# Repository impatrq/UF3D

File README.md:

# Bienvenido a UpFeet

<div align="center">

🔗 Visitanos en  
👉 <a href="vzaccari33.wixsite.com/upfeet" target="_blank" rel="noopener noreferrer"><strong>nuestra pagina web</strong></a>

<br><br>

<a href="https://www.instagram.com/upfeet.3d/" target="_blank" rel="noopener noreferrer">
  
  @upfeet
</a>

</div>

---

## Nuestra Propuesta

**UpFeet3D** es un proyecto que desarrolla un escáner de pies basado en tecnología LiDAR y un sistema de ejes motorizados que permiten generar un modelo 3D preciso de la anatomía del pie. A partir de este escaneo, se diseña de manera automática una plantilla ortopédica personalizada que luego es fabricada mediante impresión 3D, ofreciendo una solución innovadora, accesible y adaptada a cada usuario.

---

## Cómo surgió el proyecto

El proyecto surgió a partir de la necesidad de brindar una solución a los pilotos y tripulaciones aéreas, quienes pasan largas horas sentados en condiciones que, sumadas a una mala pisada, pueden afectar la postura, generar dolores en la columna y aumentar la fatiga. Para atender esta problemática se diseñó un escáner portátil, que permite a una aerolínea contar con una sola máquina capaz de realizar plantillas personalizadas a todos sus empleados, reduciendo costos y facilitando la implementación. Con el tiempo, el desarrollo se proyectó también para otros usos, ofreciendo beneficios a cualquier persona que requiera una corrección postural o mayor confort en su andar.

---

## Características Principales

- Impresión 3D  
- Configuración por pantalla táctil  
- Escaneo 3D LiDAR  
- Sistema de ejes  
- Portátil  
- Económico  
- Rápido  

---

## Integrantes

- Melina Alfonso  
- Agustín Azorín  
- Eugenio Herrera  
- Tiago López  
- Victoria Viva  
- Valentín Zaccari  

---

## Información de Contacto

🌐 Sitio web oficial: [UpFeet Web](vzaccari33.wixsite.com/upfeet)  
📸 Instagram: [@UpFeet](https://www.instagram.com/upfeet.3d/) 📱🙌🎉  
📧 Correo: **upfeet3d@gmail.com**

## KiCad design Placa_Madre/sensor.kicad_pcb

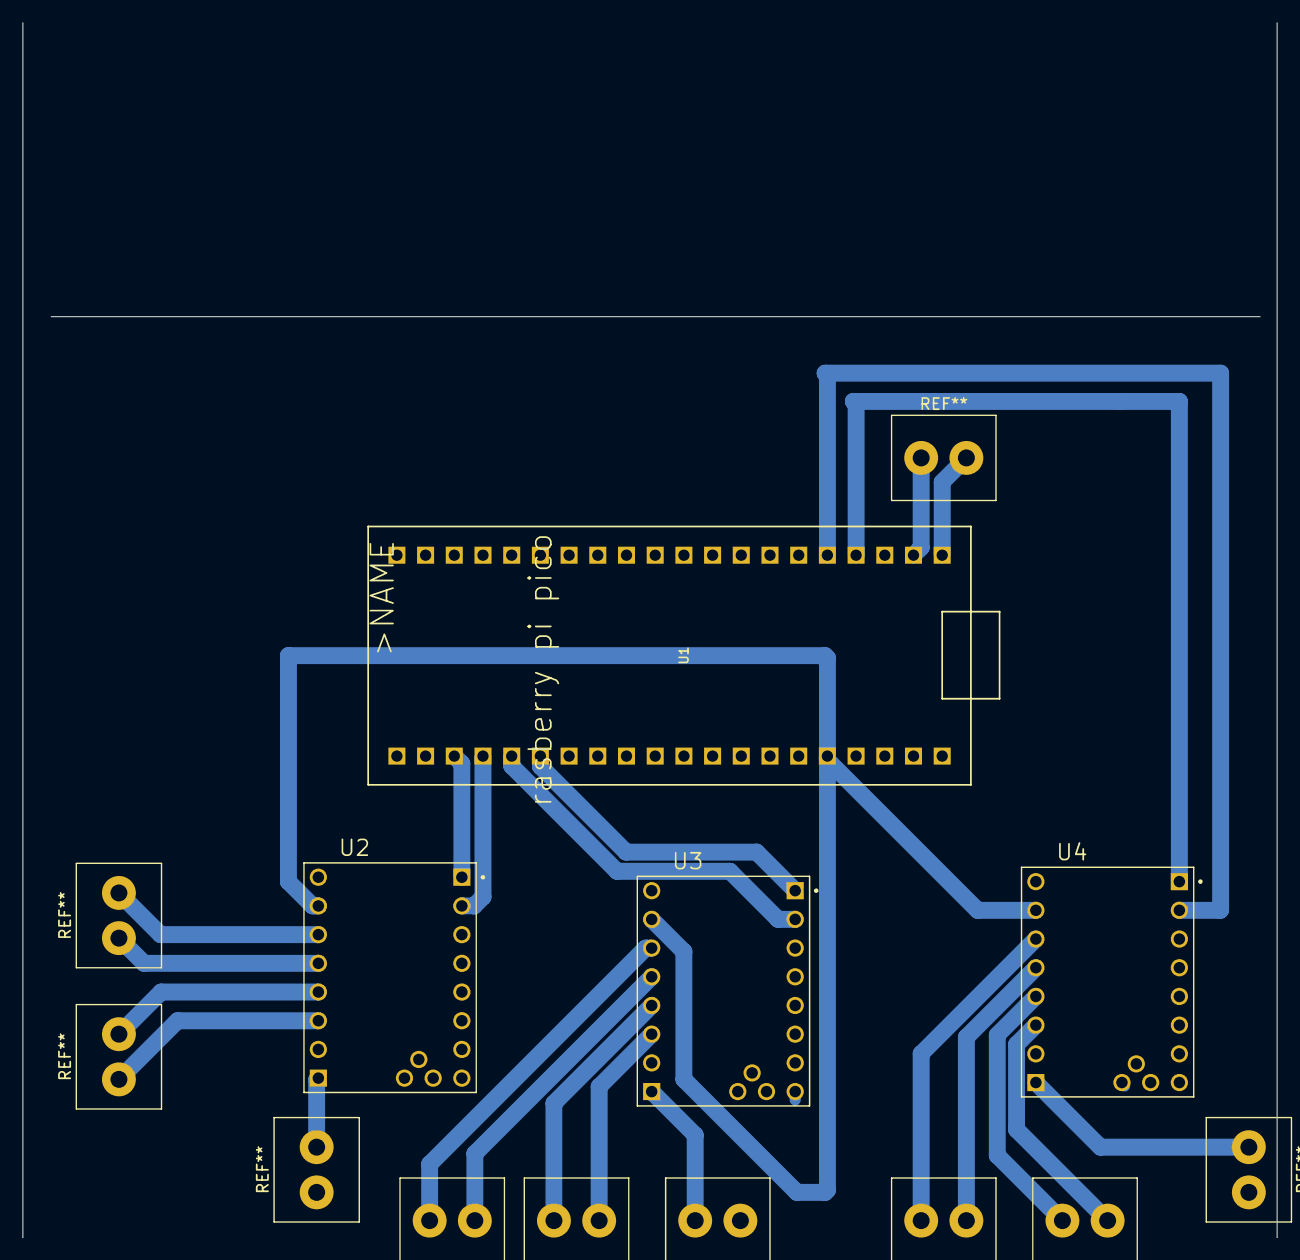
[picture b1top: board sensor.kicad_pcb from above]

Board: 2 copper layers, 111.0 x 107.5 mm, 4 parts (0 on the bottom side), 8 nets.

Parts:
U1: RASPBERRY_PI_PICO
U2, U3, U4: TMC2208_SILENTSTEPSTICK; MODULE_TMC2208_SILENTSTEPSTICK

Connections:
DIR: U1.GND3, U2.JP1_1 (DIR)
DIR2: U1.GP19, U3.JP1_2 (STEP)
DIR3: U1.GP2, U1.GP21, U4.JP1_1 (DIR)
GND: U1.GND, U2.JP1_8 (EN), U2.JP2_2 (GND), U2.JP2_8 (GND), U3.JP1_8 (EN), U3.JP2_2 (GND), U3.JP2_8 (GND), U4.JP1_8 (EN), U4.JP2_2 (GND), U4.JP2_8 (GND)
STEP1: U1.GP18, U2.JP1_2 (STEP)
STEP2: U1.GP20, U3.JP1_1 (DIR)
STEP3: U1.GP3, U1.GP22, U4.JP1_2 (STEP)
VIO: U1.3V3, U2.JP2_7 (VIO), U3.JP2_7 (VIO), U4.JP2_7 (VIO)

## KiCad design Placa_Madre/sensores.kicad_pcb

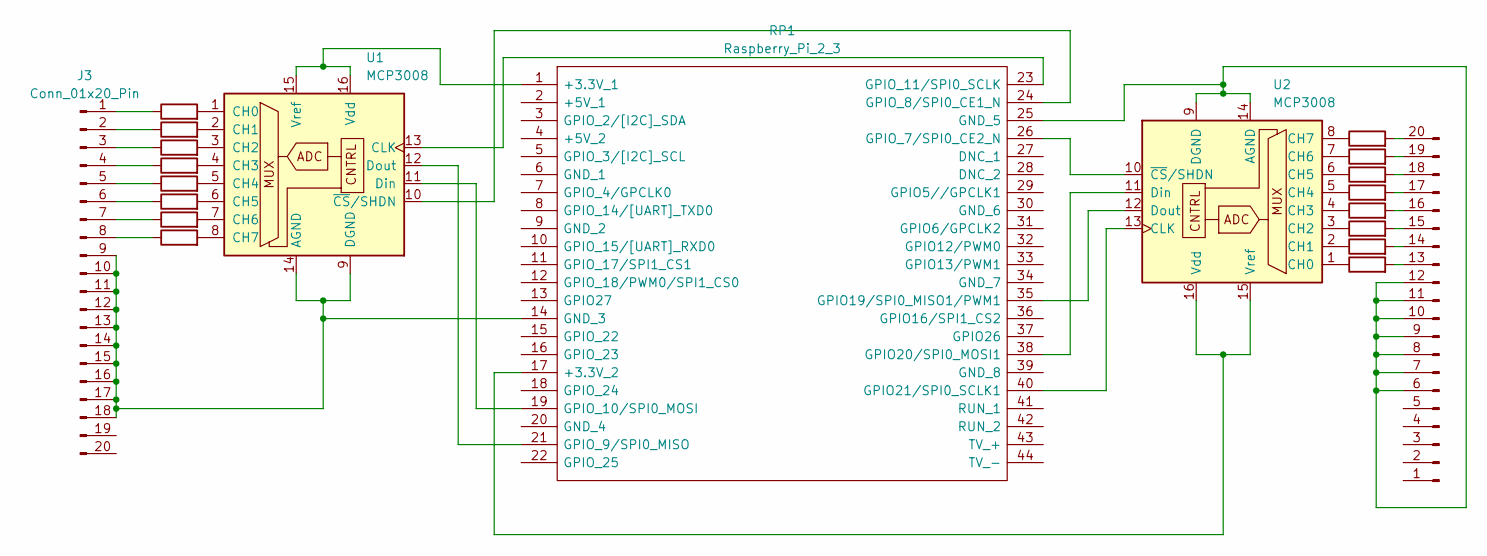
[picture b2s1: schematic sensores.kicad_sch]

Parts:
J3, J4: Conn_01x20_Pin; PinHeader_1x20_P1.00mm_Vertical
R16, R17, R18, R19, R20, R21, R22, R23, R24, R25, R26, R27, R28, R29, R30, R31: R; R_0201_0603Metric
RP1: Raspberry_Pi_2_3; MODULE_RASPBERRY_PI_4B_4GB; Manufacturer_Part_Number Raspberry Pi 2 or 3
U1, U2: MCP3008; DIP16-2.54-19.2X7.62MM

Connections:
unnamed: J3.1, R23.1
unnamed: J3.2, R22.1
unnamed: J3.3, R21.1
unnamed: J3.4, R20.1
unnamed: J3.5, R19.1
unnamed: J3.6, R18.1
unnamed: J3.7, R17.1
unnamed: J3.8, R16.1
unnamed: J3.9, J3.10, J3.11, J3.12, J3.13, J3.14, J3.15, J3.16, J3.17, J3.18, RP1.14 (GND_3), U1.9 (DGND), U1.14 (AGND)
unnamed: J4.6, J4.7, J4.8, J4.9, J4.10, J4.11, J4.12, RP1.25 (GND_5), U2.9 (DGND), U2.14 (AGND)
unnamed: J4.13, R31.2
unnamed: J4.14, R30.2
unnamed: J4.15, R29.2
unnamed: J4.16, R28.2
unnamed: J4.17, R27.2
unnamed: J4.18, R26.2
unnamed: J4.19, R25.2
unnamed: J4.20, R24.2
unnamed: RP1.1 (+3.3V_1), U1.15 (Vref), U1.16 (Vdd)
unnamed: RP1.17 (+3.3V_2), U2.15 (Vref), U2.16 (Vdd)
unnamed: RP1.35 (GPIO19/SPI0_MISO1/PWM1), U2.12 (Dout)
unnamed: RP1.38 (GPIO20/SPI0_MOSI1), U2.11 (Din)
unnamed: RP1.40 (GPIO21/SPI0_SCLK1), U2.13 (CLK)
unnamed: RP1.26 (GPIO_7/SPI0_CE2_N), U2.10 (~CS/SHDN)
unnamed: RP1.24 (GPIO_8/SPI0_CE1_N), U1.10 (~CS/SHDN)
unnamed: RP1.21 (GPIO_9/SPI0_MISO), U1.12 (Dout)
unnamed: RP1.19 (GPIO_10/SPI0_MOSI), U1.11 (Din)
unnamed: RP1.23 (GPIO_11/SPI0_SCLK), U1.13 (CLK)
unnamed: R23.2, U1.1 (CH0)
unnamed: R22.2, U1.2 (CH1)
unnamed: R21.2, U1.3 (CH2)
unnamed: R20.2, U1.4 (CH3)
unnamed: R19.2, U1.5 (CH4)
unnamed: R18.2, U1.6 (CH5)
unnamed: R17.2, U1.7 (CH6)
unnamed: R16.2, U1.8 (CH7)
unnamed: R31.1, U2.1 (CH0)
unnamed: R30.1, U2.2 (CH1)
unnamed: R29.1, U2.3 (CH2)
unnamed: R28.1, U2.4 (CH3)
unnamed: R27.1, U2.5 (CH4)
unnamed: R26.1, U2.6 (CH5)
unnamed: R25.1, U2.7 (CH6)
unnamed: R24.1, U2.8 (CH7)

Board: 2 copper layers, 21 parts (0 on the bottom side), 44 nets, no tracks yet.

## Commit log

2025-04-27 Create INFO
2025-09-17 Rename Configuration.h to Impresora/Configuration.h
2025-09-17 Rename Configuration_adv.h to Impresora/Configuration_adv.h
2025-09-22 Create Hola
2025-09-22 Dia 22
2025-09-23 Rename Abril.md to Abril.md
2025-09-23 Rename Septiembre.md to Septiembre.md
2025-09-23 Rename sensor.kicad_prl to sensor.kicad_prl
2025-09-23 Mes de la primavera🌈🌸
2025-10-20 arreglando el pcb
2025-10-21 Subiendo Mes de Abril
2025-10-21 Rename Abril.md to Documentacion/Carpeta de campo/Abril.md
2025-10-21 Subiendo Mes de Agosto
2025-10-21 Subiendo Mes de Mayo
2025-10-21 30 de noviembre
2025-10-21 Create Manual de Usuario
2025-10-21 Rename Manual de Usuario to Manual de Usuario.md
2025-10-21 Logos IMPA y ANAC
2025-10-21 Rename Logo.jpg to Documentacion/Logos/Logo.jpg
2025-10-21 Subir logo de la matelurgia
2025-10-21 Subir todos los Logos
2025-10-21 creando el encabezado
2025-10-21 cREACION DEL INDICE BOCETO
2025-10-22 Tornillos y destornilladores
    Se magrego la seccion tornillos y dstornilladores
2025-10-31 Correjir PPCB
2025-10-31 Cambio de pi 4 a pi pico
2025-10-31 Subir Manual de usuario y carpoeta tecnica
2025-11-12 Subir soportes 3D
2025-11-12 Rename Soporte_del_otro_eje.stl to Soportes_3D/Soporte_del_otro_eje.stl
2025-11-12 Rename soporte_varilla_eje_x_1.stl to Soportes_3D/soporte_varilla_eje_x_1.stl
2025-11-12 Rename Dibujo1.stl to Soportes_3D/soprote_sensor.stl
2025-11-18 Rename 027b8d05-ae66-469a-8569-234fba0616f8.jpg to Foto_banner_grupal.jpg
2025-11-18 Subir factura de la placa de cobre
2025-11-18 Rename dba2b513-6633-446f-9577-a1ffcd4fef4a.jpg to 17 de junio.jpg
2025-11-18 Factura de las varillas
2025-11-18 Factura de cables
2025-11-18 Factura corte de varillas
2025-11-18 Factura placa de cobre y cables
2025-11-18 Factura de SD
2025-11-18 Factura borneras y ficha db15
2025-11-18 Add Configuration.h for printer firmware settings
2025-11-18 Rename Configuration_adv.h to Configuration_adv.h
2025-11-18 Factura adaptador sd usb
2025-11-18 Rename 16 de septiembre.jpg to 16-09.jpg
2025-11-18 Rename 23de septiembre.jpg to 23-09.jpg
2025-11-18 Rename 27 de septiembre.jpg to 27-09.jpg
2025-11-18 Rename 4 de septiembre.jpg to 4-09.jpg
2025-11-18 Rename 5 de septiembre.jpg to 5-09.jpg
2025-11-18 Rename 9 de julio.jpg to 9-07.jpg
2025-11-18 Rename 21 de julio.jpg to 21-07.jpg
2025-11-18 Rename 17 de junio.jpg to 17-06.jpg
2025-11-18 Rename 18 de agosto.jpg to 18-08.jpg
2025-11-18 Factura drivers
2025-11-18 Factura placa de cobre
2025-11-18 Rename 21 de octubre.jpg to 21-10.jpg
2025-11-18 Rename 14de octubre.jpg to 14-10.jpg
2025-11-18 Factura tuercaas anti giro
2025-11-18 Rename 4 de noviembre.jpg to 4-11.jpg
2025-11-18 Rename 11 de septiembre.jpg to 11-09.jpg
2025-11-18 Create elemenos de alcance inconclusos
2025-11-18 Banner
2025-11-18 Diapositiva de presentación
2025-11-18 Subir octubre y noviembre
2025-11-18 Rename noviembre-2.md to noviembre.md
2025-11-22 Rename Dibujo1.dwg to Dibujo1.dwg
2025-11-22 Rename soporte.dwg to soporte.dwg
2025-11-22 Rename Soporte_3D/soporte.dwg to Soportes_3Dsoporte.dwg
2025-11-22 Create impresora2
2025-11-22 Rename Dibujo1.dwg to chasis escaner.dwg
2025-11-22 Rename Video de WhatsApp 2025-11-22 a las 15.33.45_e74085b7.mp4 to probando motores
2025-11-22 Rename Imagen de WhatsApp 2025-11-22 a las 15.33.41_6b8152f8.jpg to paralelo de sensores
2025-11-22 Rename Imagen de WhatsApp 2025-11-22 a las 15.33.40_7c466ca6.jpg to probando motores con la placa skr1.4
2025-11-22 Rename Imagen de WhatsApp 2025-11-22 a las 15.33.40_4c03e847.jpg to probando ventiladores
2025-11-22 Rename Video de WhatsApp 2025-11-22 a las 15.33.45_e74085b7 (1).mp4 to primera impresion
2025-11-22 Rename Soportes_3Dsoporte.dwg to Soportes_3D/soporte.dwg
2025-11-22 Rename fotos_impresora/paralelo de sensores to Documentacion/Imagenes/Impresora/paralelo de sensores
2025-11-22 Rename fotos_impresora/primera impresion to Documentacion/Imagenes/Impresora/primera impresion
2025-11-22 Rename fotos_impresora/probando motores to Documentacion/Imagenes/Impresora/probando motores
2025-11-22 Rename fotos_impresora/probando motores con la placa skr1.4 to Documentacion/Imagenes/Impresoraprobando motores con la placa skr1.4
2025-11-22 Rename fotos_impresora/probando ventiladores to Documentacion/Imagenes/Impresora/probando ventiladores
2025-11-22 Rename Documentacion/Imagenes/Impresoraprobando motores con la placa skr1.4 to Documentacion/Imagenes/Impresora/probando motores con la placa skr1.4
2025-11-25 Rename Manual de usuario (2).pdf to Manual de usuario.pdf
2025-11-25 Rename Informe tecnico (2).pdf to Informe tecnico.pdf
2025-11-25 Rename Informe_Falla_SKR_V1.4.pdf to Informe Falla SKR V1.4.pdf
2025-11-25 Create Code
2025-11-25 Rename Code to Code-code
2025-11-25 Create -code
2025-11-27 Rename Informe tecnico (3).pdf to Informe tecnico.pdf
2025-11-28 Rename Informe Fallas (6).pdf to Informe Fallas.pdf
